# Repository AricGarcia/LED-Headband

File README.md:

# LED-Headband
Source code for Attiny85 top level control code and LP5562 slave code.

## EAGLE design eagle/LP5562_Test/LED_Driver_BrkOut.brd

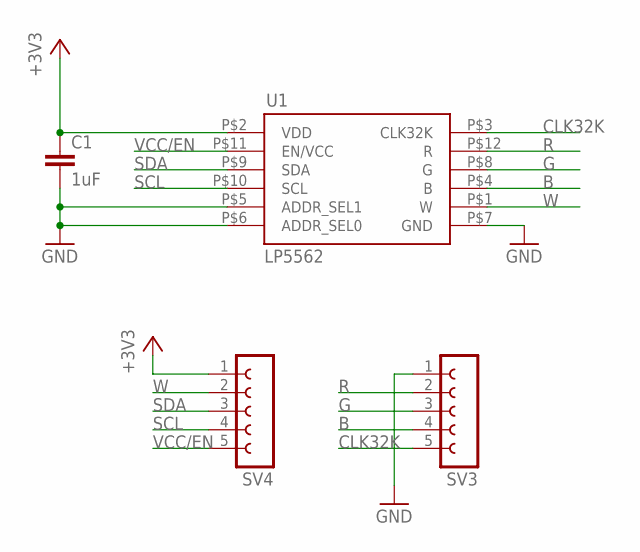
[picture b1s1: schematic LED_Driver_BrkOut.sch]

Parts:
C1: 1uF; C0603
SV3, SV4: FE05-1
U1: LP5562; YQE_12-PIN_DSBGA

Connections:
+3V3: C1.1, SV4.1, U1.P$2 (VDD)
B: SV3.4, U1.P$4 (B)
CLK32K: SV3.5, U1.P$3 (CLK32K)
G: SV3.3, U1.P$8 (G)
GND: C1.2, SV3.1, U1.P$5 (ADDR_SEL1), U1.P$6 (ADDR_SEL0), U1.P$7 (GND)
R: SV3.2, U1.P$12 (R)
SCL: SV4.4, U1.P$10 (SCL)
SDA: SV4.3, U1.P$9 (SDA)
VCC/EN: SV4.5, U1.P$11 (EN/VCC)
W: SV4.2, U1.P$1 (W)

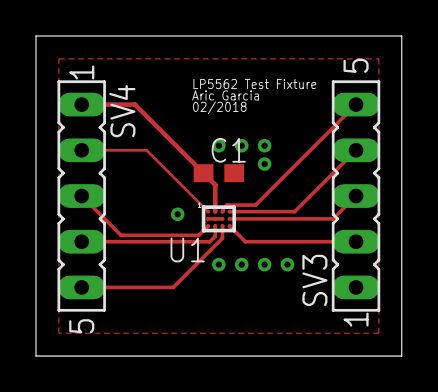
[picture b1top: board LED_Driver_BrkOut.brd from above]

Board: 2 copper layers, 20.3 x 17.8 mm, 4 parts (0 on the bottom side), 10 nets.

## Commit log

2017-11-21 Initial commit of LED headband code base
2017-11-22 Updates to Lib files
2017-11-27 Updates to several functions and some new additions
2017-11-27 turning returns to continues
2017-11-28 Additions to LP5562
2017-12-02 Adding keyword.txt
2017-12-02 Created zipped lib
2017-12-02 Fixing error in h file
2017-12-02 adding new zip file
2017-12-04 Completion of LP5562 Lib
2018-03-05 adding eagle files
